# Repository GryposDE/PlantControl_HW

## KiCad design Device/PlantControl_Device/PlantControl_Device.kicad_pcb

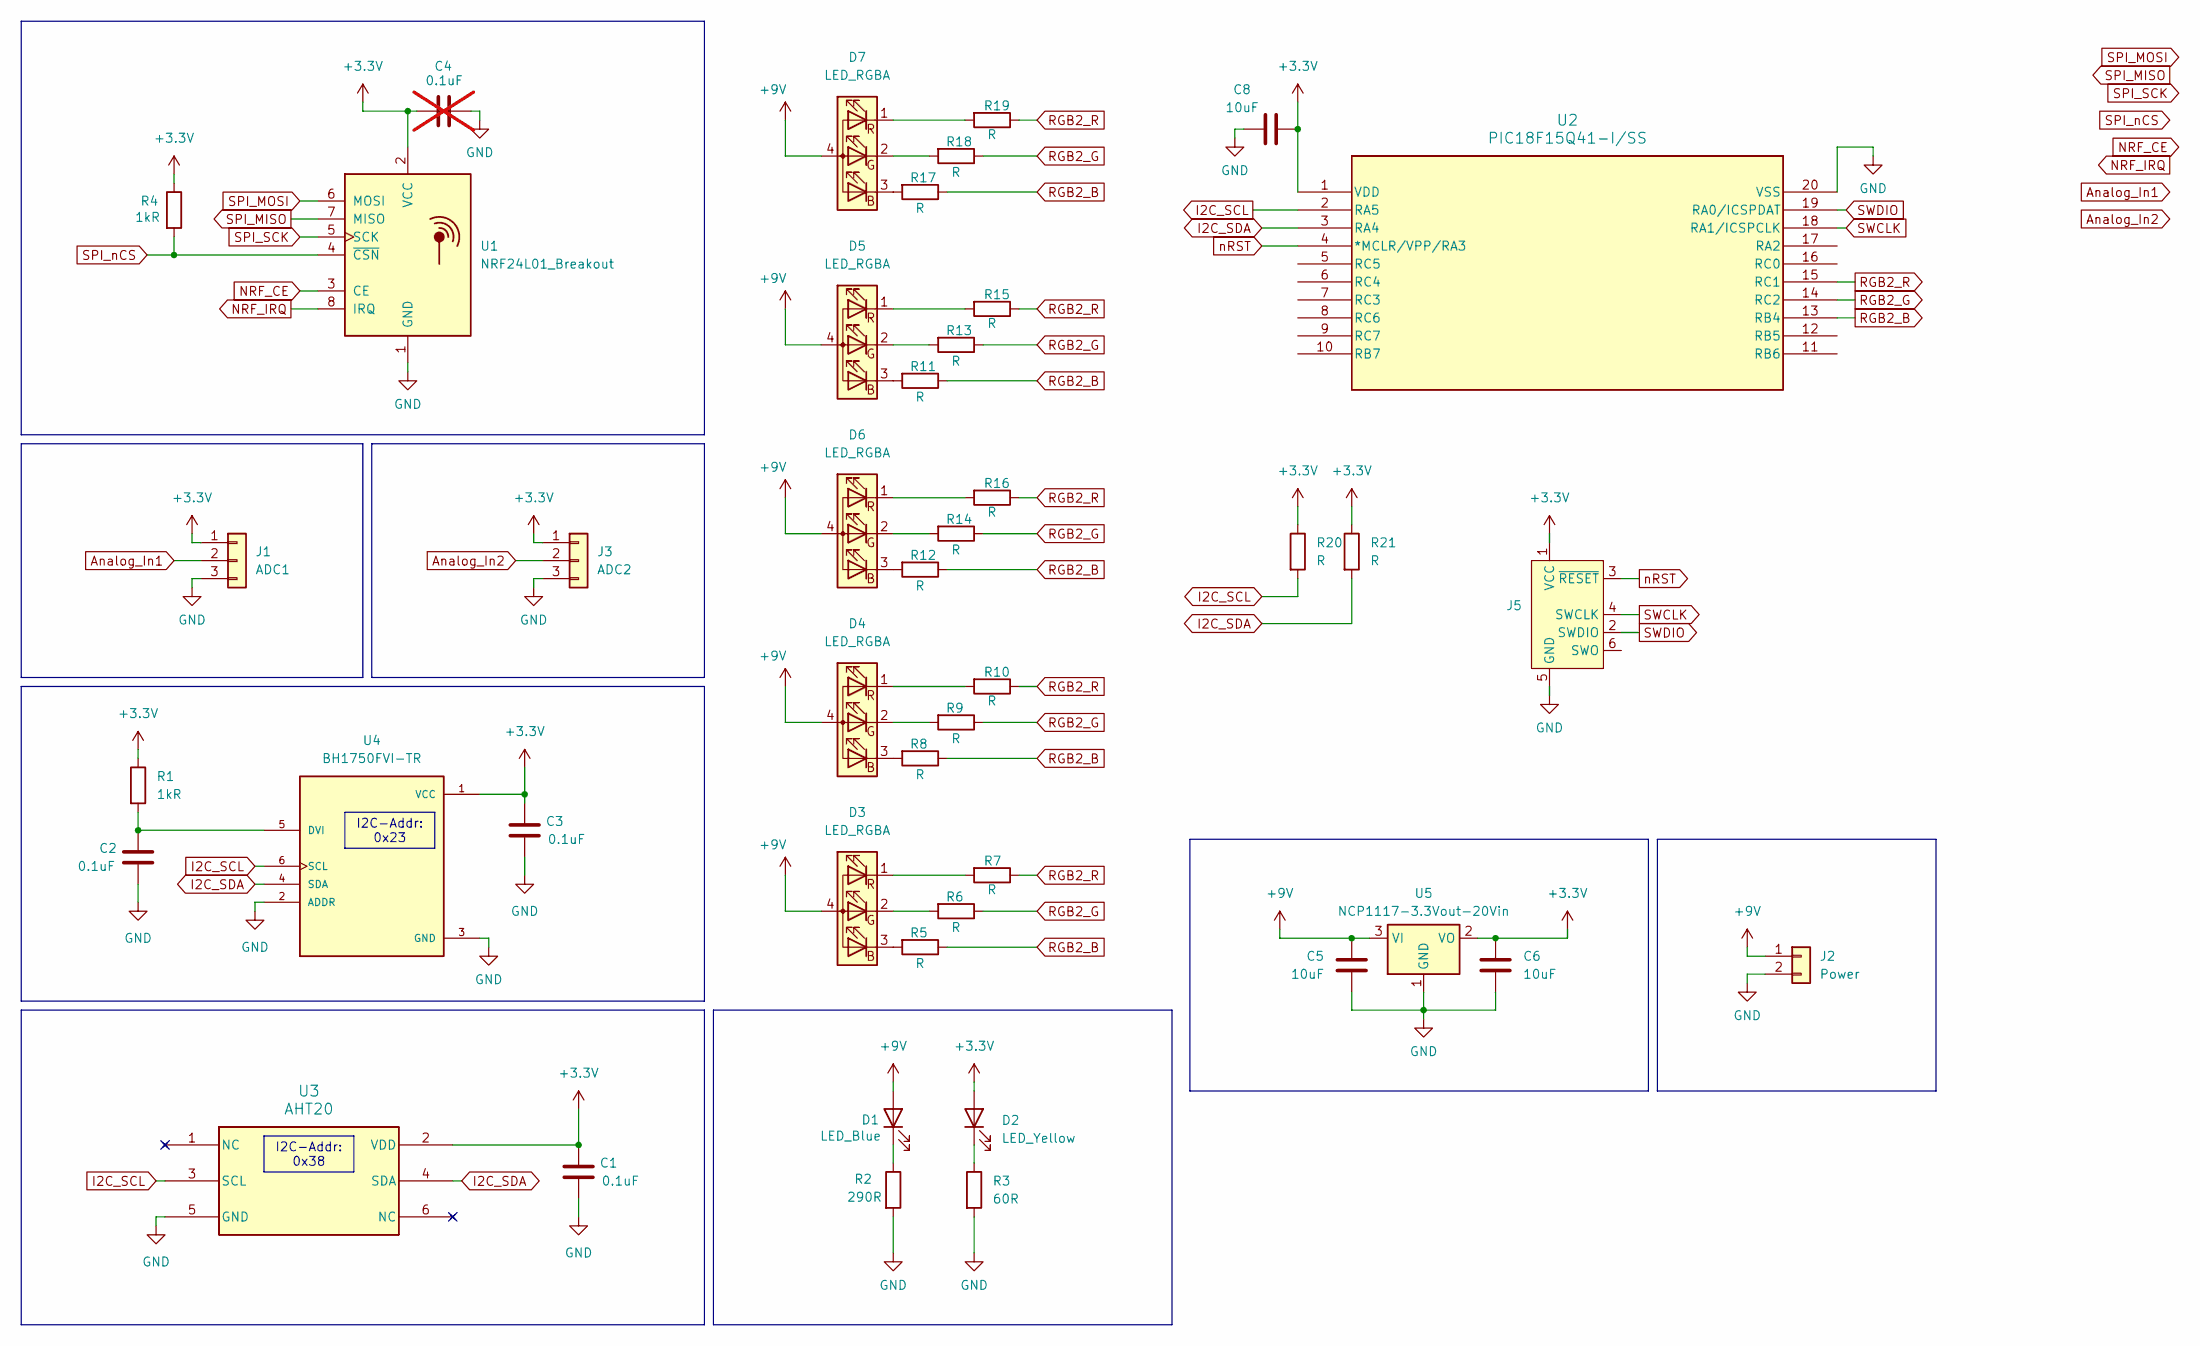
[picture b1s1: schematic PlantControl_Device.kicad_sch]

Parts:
C1, C2, C3: 0.1uF; C_0805_2012Metric_Pad1.18x1.45mm_HandSolder
C4: 0.1uF; C_0805_2012Metric_Pad1.18x1.45mm_HandSolder; not fitted
C5, C6: 10uF; C_0805_2012Metric_Pad1.18x1.45mm_HandSolder
C8: 10uF; C_Disc_D4.3mm_W1.9mm_P5.00mm
D1: LED_Blue; LED_0805_2012Metric_Pad1.15x1.40mm_HandSolder
D2: LED_Yellow; LED_0805_2012Metric_Pad1.15x1.40mm_HandSolder
D3, D4, D5, D6, D7: LED_RGBA; cr_RGB_LED
J1: ADC1; PinHeader_1x03_P2.00mm_Vertical
J2: Power; PinHeader_1x02_P2.00mm_Vertical
J3: ADC2; PinHeader_1x03_P2.00mm_Vertical
J5: Conn_ARM_SWD_TagConnect_TC2030-NL; Tag-Connect_TC2030-IDC-NL_2x03_P1.27mm_Vertical
R1, R4: 1kR; R_0805_2012Metric_Pad1.20x1.40mm_HandSolder
R2: 290R; R_0805_2012Metric_Pad1.20x1.40mm_HandSolder
R3: 60R; R_0805_2012Metric_Pad1.20x1.40mm_HandSolder
R5, R6, R7, R8, R9, R10, R11, R12, R13, R14, R15, R16, R17, R18, R19: R; R_Axial_DIN0207_L6.3mm_D2.5mm_P7.62mm_Horizontal
R20, R21: R; R_0805_2012Metric_Pad1.20x1.40mm_HandSolder
U1: NRF24L01_Breakout; nRF24L01_Breakout
U2: PIC18F15Q41-I/SS; SSOP20_SS_MCH
U3: AHT20; AHT20_GAE
U4: BH1750FVI-TR; XDCR_BH1750FVI-TR; PARTREV D
U5: NCP1117-3.3Vout-20Vin; SOT-223-3_TabPin2

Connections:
+3.3V: C1.2, C3.2, C4.2, C6.1, C8.2, D2.2 (A), J1.1, J3.1, J5.1 (VCC), R1.1, R4.1, R20.1, R21.1, U1.2 (VCC), U2.1 (VDD), U3.2 (VDD), U4.1 (VCC), U5.2 (VO)
+9V: C5.1, D1.2 (A), D3.4 (A), D4.4 (A), D5.4 (A), D6.4 (A), D7.4 (A), J2.1, U5.3 (VI)
Analog_In1: J1.2
Analog_In2: J3.2
GND: C1.1, C2.1, C3.1, C4.1, C5.2, C6.2, C8.1, J1.3, J2.2, J3.3, J5.5 (GND), R2.2, R3.2, U1.1 (GND), U2.20 (VSS), U3.5 (GND), U4.2 (ADDR), U4.3 (GND), U5.1 (GND)
I2C_SCL: R20.2, U2.2 (RA5), U3.3 (SCL), U4.6 (SCL)
I2C_SDA: R21.2, U2.3 (RA4), U3.4 (SDA), U4.4 (SDA)
NRF_CE: U1.3 (CE)
NRF_IRQ: U1.8 (IRQ)
unnamed: D1.1 (K), R2.1
unnamed: D2.1 (K), R3.1
unnamed: D3.3 (BK), R5.2
unnamed: D3.2 (GK), R6.2
unnamed: D3.1 (RK), R7.2
unnamed: D4.3 (BK), R8.2
unnamed: D4.2 (GK), R9.2
unnamed: D4.1 (RK), R10.2
unnamed: D5.3 (BK), R11.2
unnamed: D5.2 (GK), R13.2
unnamed: D5.1 (RK), R15.2
unnamed: D6.3 (BK), R12.2
unnamed: D6.2 (GK), R14.2
unnamed: D6.1 (RK), R16.2
unnamed: D7.3 (BK), R17.2
unnamed: D7.2 (GK), R18.2
unnamed: D7.1 (RK), R19.2
unnamed: C2.2, R1.2, U4.5 (DVI)
RGB2_B: R5.1, R8.1, R11.1, R12.1, R17.1, U2.13 (RB4)
RGB2_G: R6.1, R9.1, R13.1, R14.1, R18.1, U2.14 (RC2)
RGB2_R: R7.1, R10.1, R15.1, R16.1, R19.1, U2.15 (RC1)
SPI_MISO: U1.7 (MISO)
SPI_MOSI: U1.6 (MOSI)
SPI_SCK: U1.5 (SCK)
SPI_nCS: R4.2, U1.4 (~CSN)
SWCLK: J5.4 (SWCLK), U2.18 (RA1/ICSPCLK)
SWDIO: J5.2 (SWDIO), U2.19 (RA0/ICSPDAT)
nRST: J5.3 (~RESET), U2.4 (*MCLR/VPP/RA3)

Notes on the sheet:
I2C-Addr: 0x38
I2C-Addr: 0x23

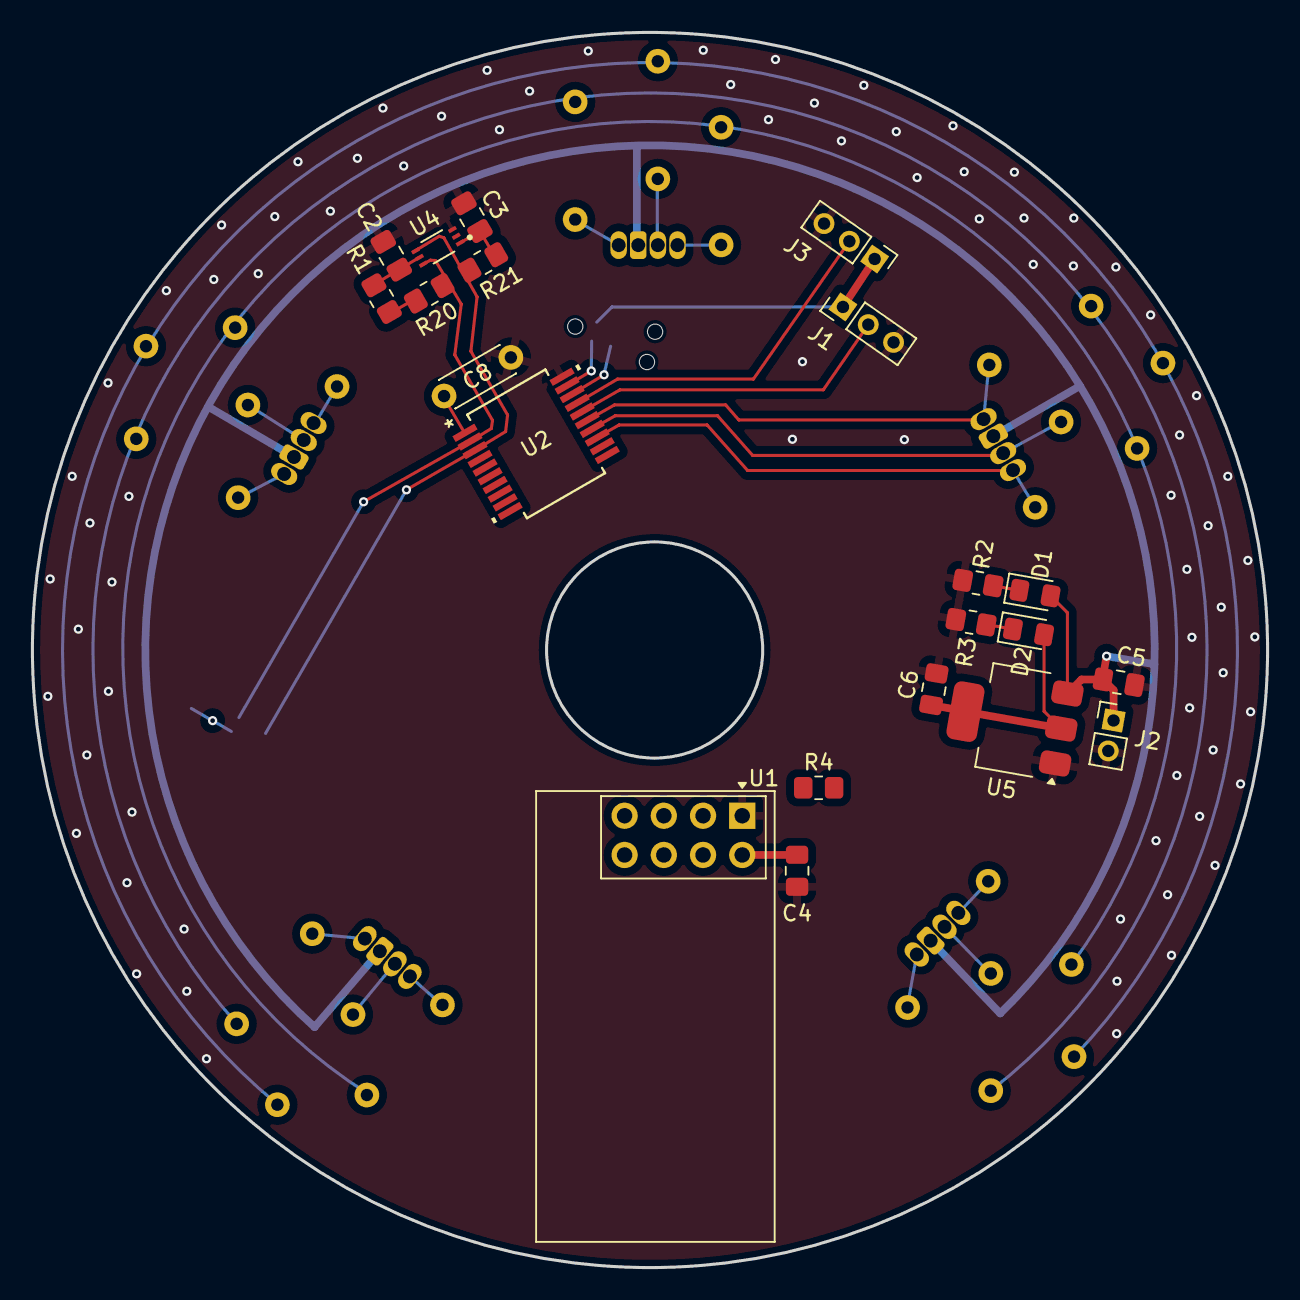
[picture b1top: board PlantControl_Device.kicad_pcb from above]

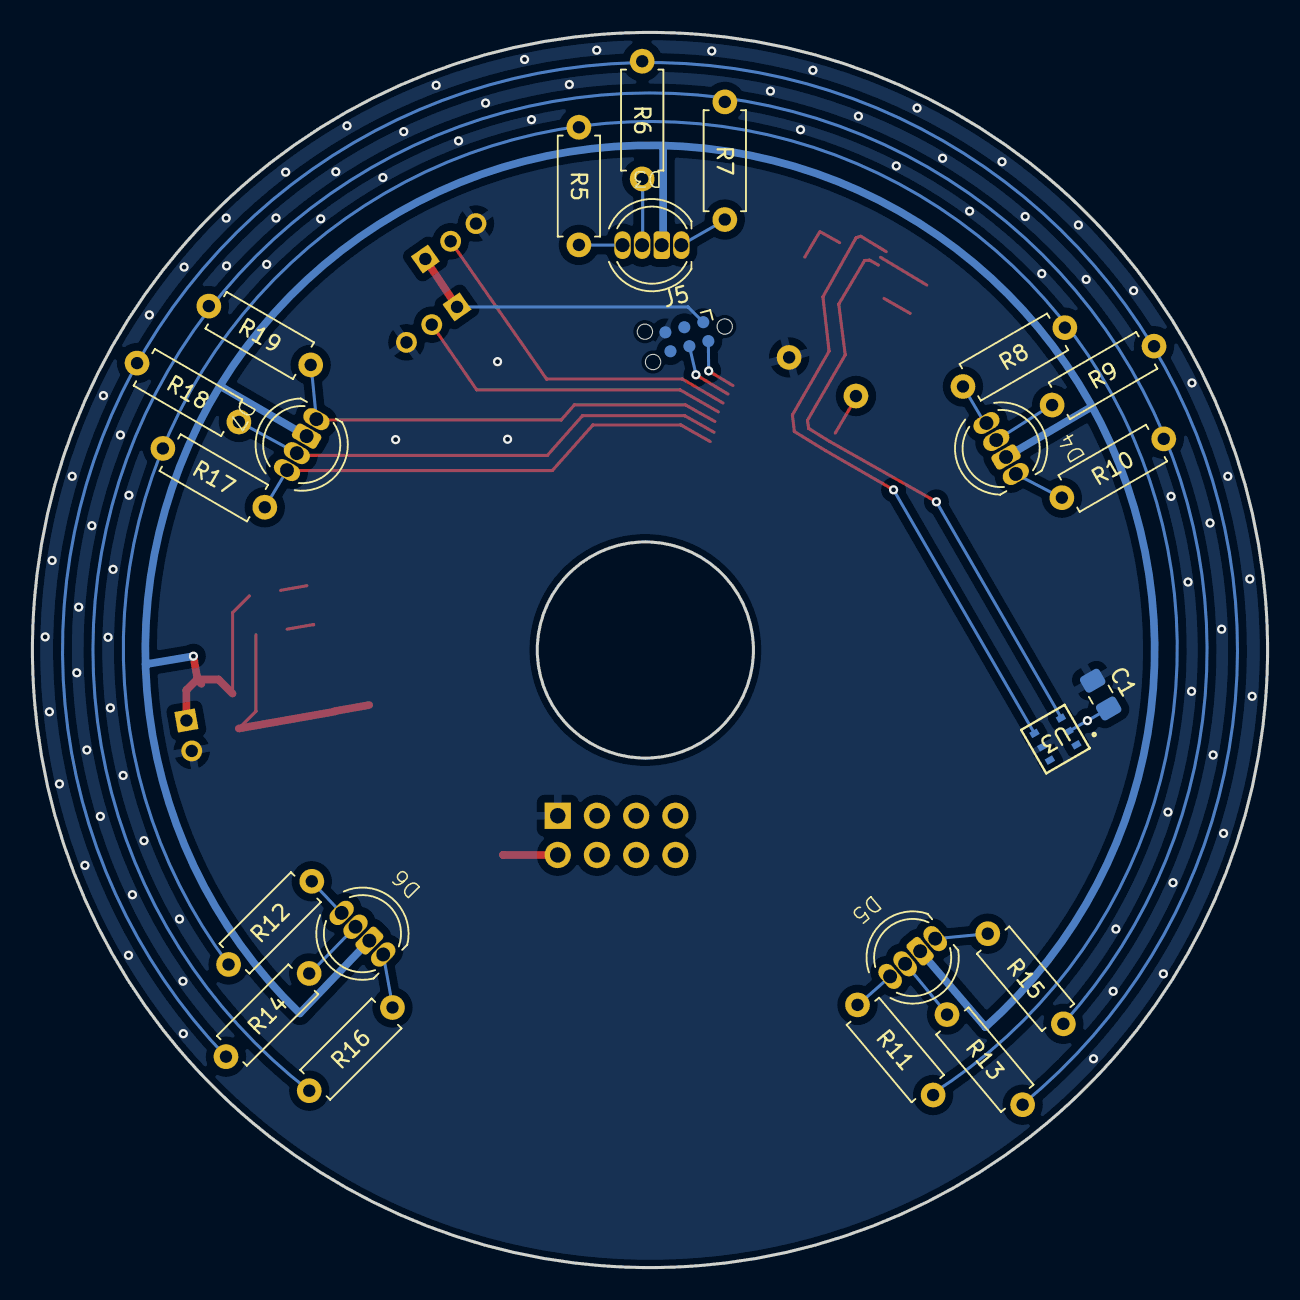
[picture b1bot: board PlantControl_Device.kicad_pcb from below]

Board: 2 copper layers, 80.0 x 80.0 mm, 44 parts (23 on the bottom side), 30 nets.

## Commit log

2025-08-03 Added Power stuff in schematic + gitignore file
2025-08-03 Added PowerGood LEDs for 9V and 3.3V
2025-08-03 Added "fp-info-cache" to gitignore and deleted it
2025-08-03 Added labels
2025-08-03 First layout
